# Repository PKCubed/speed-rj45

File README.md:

# Speed-rj45
A game in which the player's compete to correctly terminate rj45 connections the fastest.

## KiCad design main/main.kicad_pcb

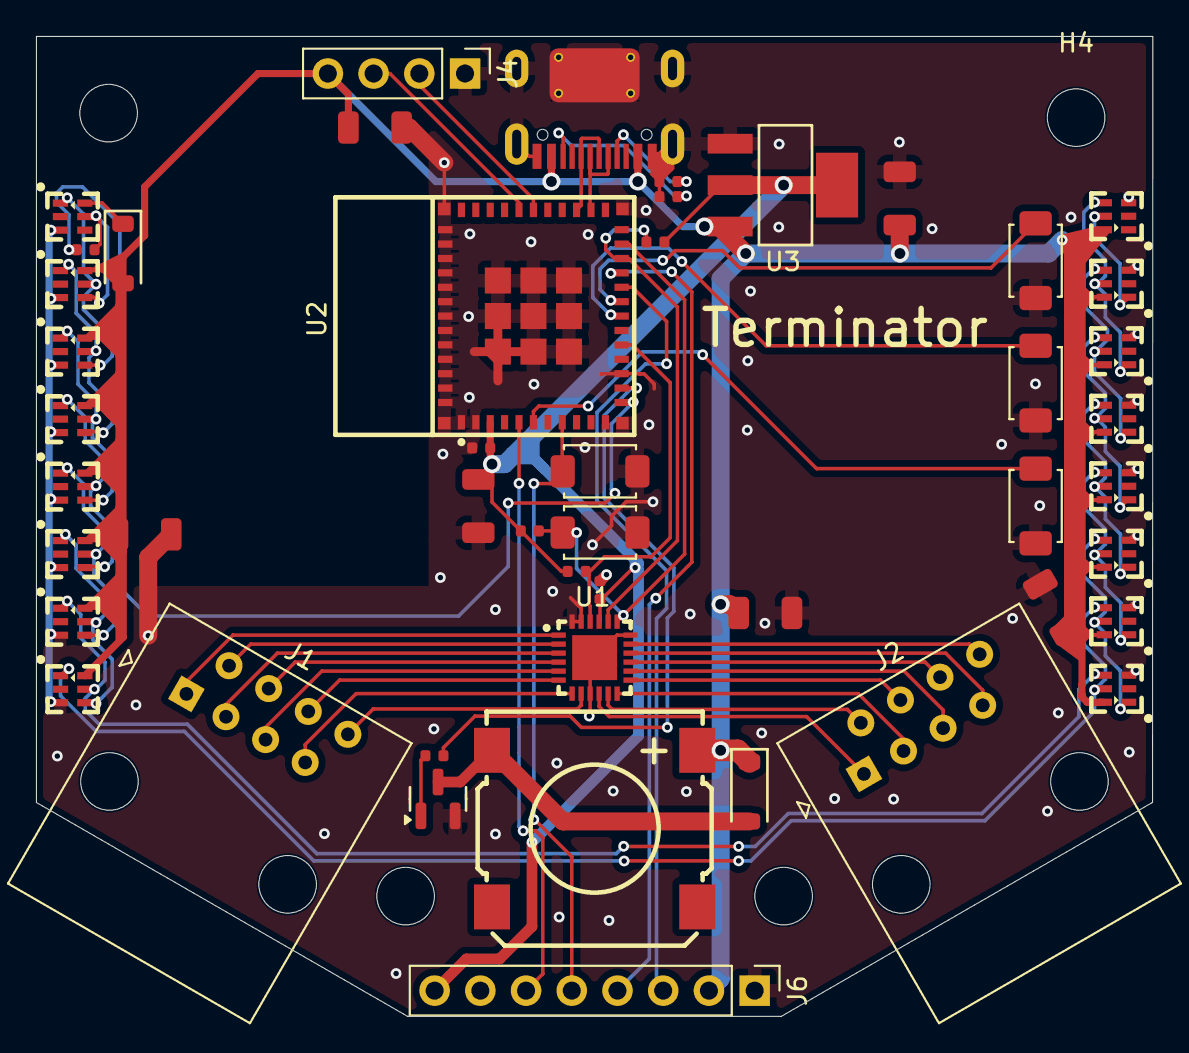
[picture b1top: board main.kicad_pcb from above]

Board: 2 copper layers, 62.0 x 54.4 mm, 52 parts (0 on the bottom side), 56 nets.

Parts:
C1, C7: 100nF; C_0402
C2, C3, C4, C5, C6, C9: 47uF; C_1206
D1, D2: 1N4148W; D_SOD-123
H1, H2, H3, H4: MountingHole; MountingHole_3.2mm_M3
J1, J2: RJ45; RJ45_Amphenol_54602-x08_Horizontal
J3: Connector, USB-TYPE-C-16P; TYPE-C-SMD_HX-TYPE-C-16PIN
J4: Conn_01x04_Pin; PinHeader_1x04_P2.54mm_Vertical
J6: Conn_01x08_Pin; PinHeader_1x08_P2.54mm_Vertical
Q1: MMBT3904; Q_SOT-23
R1, R2: 5.1kΩ; R_0402
R3: 1kΩ; R_0402
R4, R5, R7: 4.7kΩ; R_0402
R6: 330Ω; R_0402
S1, S2, S3, S4, S5: Tactile Button, 160gf; SW_TS-1088-AR02016
U1: HWQFN-24_L4.0-W4.0-P0.50-TL-EP2.5
U2: 2.4GHz; WIFIM-SMD_ESP32-C3-MINI-1
U3: SOT-223-3_L6.5-W3.4-P2.30-LS7.0-BR
U4, U5, U6, U7, U8, U9, U10, U11, U12, U13, U14, U15, U16, U17, U18, U19: LED-SMD_6P-L2.0-W2.0_XL-2020RGBC
U20: BUZ-SMD_4P-L13.0-W13.0-P11.4-BL

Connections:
+3.3V: C1.1, C6.1, C7.1, J6.8, R4.2, R5.2, R7.1, U1.21 (VCC), U2.3 (3V3), U3.2 (VOUT), U3.4 (VOUT)
+5V: C2.1, C3.1, C4.1, C5.1, C9.1, D1.1, D2.2, J3.A9B4 (VBUS), J3.B9A4 (VBUS), J4.4, J6.2, U3.3 (VIN), U5.6 (VDD), U6.6 (VDD), U7.6 (VDD), U8.6 (VDD), U9.6 (VDD), U10.6 (VDD), U11.6 (VDD), U12.6 (VDD), U13.6 (VDD), U14.6 (VDD), U15.6 (VDD), U16.6 (VDD), U17.6 (VDD), U18.6 (VDD), U19.6 (VDD), U20.1 (LEAD+)
/BOOT: R4.1, S2.2 (B), U1.19 (SCL), U2.23 (IO9)
/BTN1: S3.1 (A), U2.6 (IO3)
/BTN2: S4.1 (A), U2.18 (IO4)
/BTN3: S5.1 (A), U2.19 (IO5)
/D+: J3.A6 (D+), J3.B6 (D+), U2.27 (IO19)
/D-: J3.A7 (D-), J3.B7 (D-), U2.26 (IO18)
/DC: J6.6, U2.5 (IO2)
/EN: J6.5, S1.2 (B), U2.8 (EN)
/IO_INT: R7.2, U1.22 (INT#), U2.16 (IO10)
/MOSI: J6.4, U2.21 (IO7)
/P1_1: J1.1, U1.1 (P00)
/P1_2: J1.2, U1.2 (P01)
/P1_3: J1.3, U1.3 (P02)
/P1_4: J1.4, U1.4 (P03)
/P1_5: J1.5, U1.5 (P04)
/P1_6: J1.6, U1.6 (P05)
/P1_7: J1.7, U1.7 (P06)
/P1_8: J1.8, U1.8 (P07)
/P2_1: J2.1, U1.10
/P2_2: J2.2, U1.11
/P2_3: J2.3, U1.12
/P2_4: J2.4, U1.13
/P2_5: J2.5, U1.14
/P2_6: J2.6, U1.15
/P2_7: J2.7, U1.16
/P2_8: J2.8, U1.17
/SCK: J6.3, U2.20 (IO6)
/SDA: R5.1, U1.20 (SDA), U2.22 (IO8)
/SPK: R3.1, U2.13 (IO1)
/WS2812: R6.1, U2.12 (IO0)
GND: C1.2, C2.2, C3.2, C4.2, C5.2, C6.2, C7.2, C9.2, J3.A12B1 (GND), J3.B12A1 (GND), J3.S1 (SHIELD), J4.1, J6.1, J6.7, Q1.2 (E), R1.2, R2.1, S1.1 (A), S2.1 (A), S3.2 (B), S4.2 (B), S5.2 (B), U1.9 (GN), U1.18 (A0), U1.23 (A1), U1.24 (A2), U1.25 (EP), U2.1 (GND), U2.2 (GND), U2.11 (GND), U2.14 (GND), U2.36 (GND), U2.37 (GND), U2.38 (GND), U2.39 (GND), U2.40 (GND), U2.41 (GND), U2.42 (GND), U2.43 (GND), U2.44 (GND), U2.45 (GND), U2.46 (GND), U2.47 (GND), U2.48 (GND), U2.49 (GND), U2.50 (GND), U2.51 (GND), U2.52 (GND), U2.53 (GND), U3.1 (GND), U4.3 (GND), U5.3 (GND), U6.3 (GND), U7.3 (GND), U8.3 (GND), U9.3 (GND), U10.3 (GND), U11.3 (GND), U12.3 (GND), U13.3 (GND), U14.3 (GND), U15.3 (GND), U16.3 (GND), U17.3 (GND), U18.3 (GND), U19.3 (GND)
unnamed: J3.A5 (CC1), R1.1
unnamed: J3.B5 (CC2), R2.2
unnamed: J4.2, U2.30 (RXD0)
unnamed: J4.3, U2.31 (TXD0)
unnamed: Q1.1 (B), R3.2
unnamed: D1.2, Q1.3 (C), U20.2 (LEAD-)
unnamed: R6.2, U4.5 (DI1), U5.4 (DI2)
unnamed: U4.1 (DO), U5.5 (DI1), U6.4 (DI2)
unnamed: D2.1, U4.6 (VDD)
unnamed: U5.1 (DO), U6.5 (DI1), U7.4 (DI2)
unnamed: U6.1 (DO), U7.5 (DI1), U8.4 (DI2)
unnamed: U7.1 (DO), U8.5 (DI1), U9.4 (DI2)
unnamed: U9.1 (DO), U10.5 (DI1), U11.4 (DI2)
unnamed: U8.1 (DO), U9.5 (DI1), U10.4 (DI2)
unnamed: U10.1 (DO), U11.5 (DI1), U12.4 (DI2)
unnamed: U11.1 (DO), U12.5 (DI1), U13.4 (DI2)
unnamed: U12.1 (DO), U13.5 (DI1), U14.4 (DI2)
unnamed: U13.1 (DO), U14.5 (DI1), U15.4 (DI2)
unnamed: U14.1 (DO), U15.5 (DI1), U16.4 (DI2)
unnamed: U15.1 (DO), U16.5 (DI1), U17.4 (DI2)
unnamed: U16.1 (DO), U17.5 (DI1), U18.4 (DI2)
unnamed: U17.1 (DO), U18.5 (DI1), U19.4 (DI2)
unnamed: U18.1 (DO), U19.5 (DI1)
